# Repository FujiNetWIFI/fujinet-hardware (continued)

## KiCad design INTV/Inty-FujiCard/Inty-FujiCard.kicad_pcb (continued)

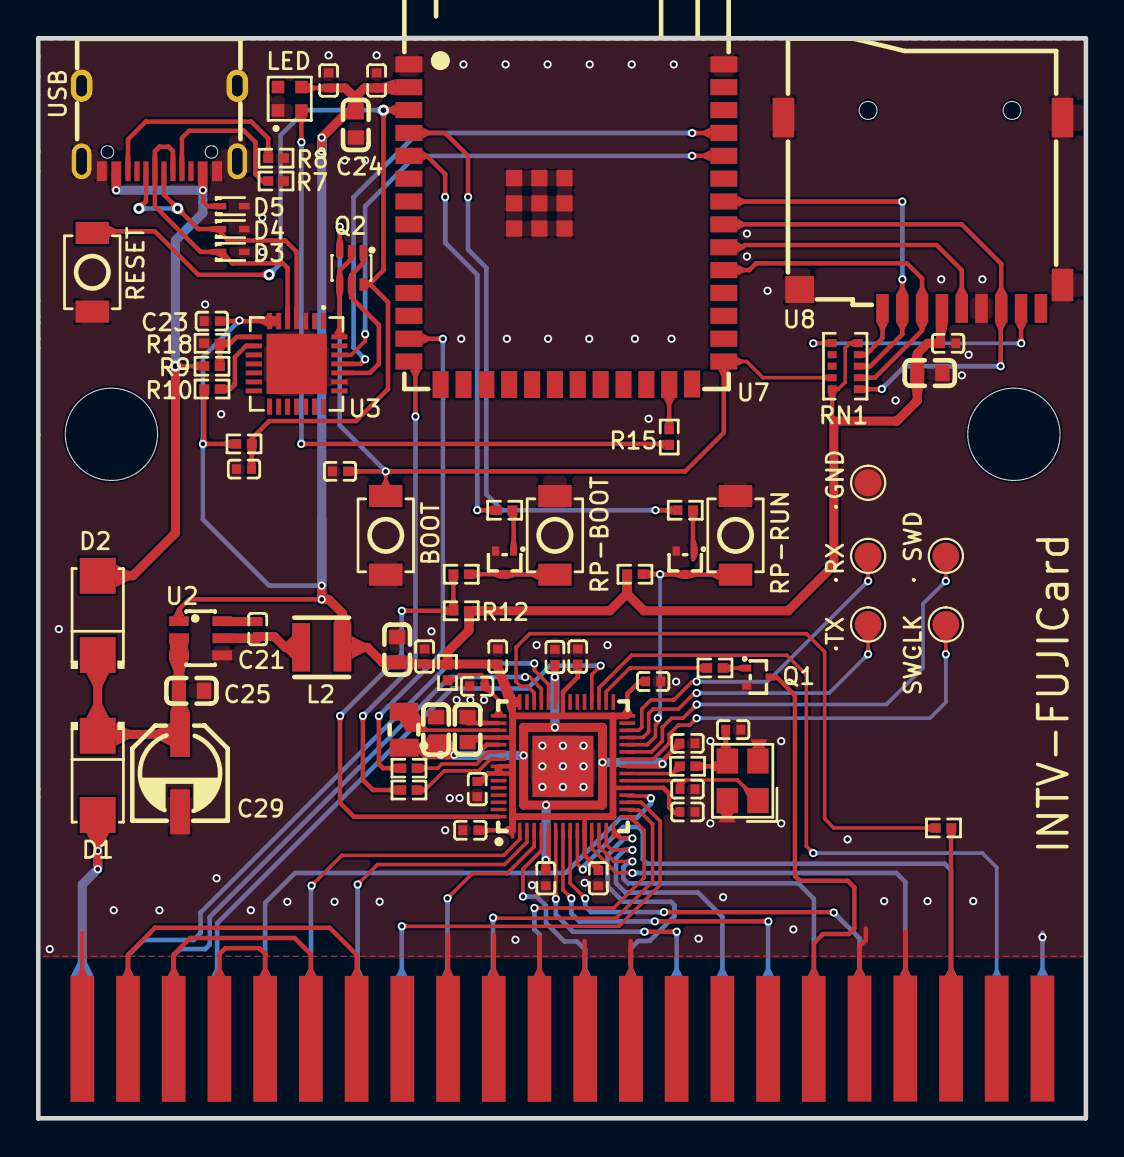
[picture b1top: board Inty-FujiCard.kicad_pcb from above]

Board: 2 copper layers, 58.2 x 60.0 mm, 78 parts (0 on the bottom side), 76 nets.

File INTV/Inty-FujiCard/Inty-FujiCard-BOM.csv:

Qty,References,Value,Footprint,MPN,Manufacturer,LCSC,Description,Notes
17,C1 C3 C7 C8 C9 C10 C11 C12 C13 C14 C15 C16 C21 C22 C23 C26 C27,100nF,C0402,CL05B104KO5NNNC,SAMSUNG,C1525,capacitor (several uses: see schematic),
1,C2,1uF,C0402,CL05A105KA5NQNC,SAMSUNG,C52923,EN power-on delay,
2,C4 C24,22uF,C0603,CL10A226MQ8NRNC,SAMSUNG,C59461,capacitor (several uses: see schematic),
2,C5 C6,15pF,C0402,0402CG150J500NT,FH,C1548,crystal load,
2,C17 C18,4.7uF,C0603,CL10A475KO8NNNC,SAMSUNG,C19666,capacitor (several uses: see schematic),
1,C19,4.7uF,C0402,CL05A475MP5NRNC,SAMSUNG,C23733,VREG_AVDD RC filter (C_FILT),
2,C25 C28,10uF,C0603,CL10A106KP8NNNC,SAMSUNG,C19702,capacitor (several uses: see schematic),
1,C29,100uF,CAP-SMD_BD5.0-L5.3-W5.3-RD,VE-101M1ATR-0505,Lelon,C134722,VIN bulk,
2,D1 D2,SS34,SMA_L4.3-W2.6-LS5.2-RD,SS34,MDD,C8678,diode (several uses: see schematic),
3,D3 D4 D5,ESD5Z5.0T1G,SOD-523_L1.2-W0.8-LS1.6-RD,ESD5Z5.0T1G,BORN,C343989,diode (several uses: see schematic),
1,D6,SK6805-EC20,LED-SMD_4P-L2.0-W2.0-TL_J-ST2020RGB-IC-P4-5-SO1,SK6805-EC20,OPSCO Optoelectronics,C2890036,"status LED (IO48), on 3V3",
2,H1 H2,Hole_D5.127mm,Hole_D5.127mm_NPTH,,,,"shell post hole, 5.127 mm NPTH",not in BOM
1,J1,USB-C,USB-C-SMD_TYPE-C-6PIN-2MD-073,TYPE-C 16PIN 2MD(073),SHOU HAN,C2765186,power + S3 programming / console,
1,K1,INTV_Cart_Edge_44,PCB_EDGE_CONNECTOR_22X2,,,,"Intellivision cartridge edge, 2 x 22 gold fingers, 2.54 mm: A1-A22 component face, B1-B22 back",not in BOM
1,L1,3.3uH,IND-SMD_L2.0-W1.6_AOTA-B201610S3R3-101-T,AOTA-B201610S3R3-101-T,ABRACON,C42411119,RP2350 core SMPS inductor,
1,L2,4.7uH,IND-SMD_L3.0-W3.0-1,YNR3015-4R7M,YJYCOIN,C340361,buck inductor,
3,Q1 Q3 Q4,BC847BT,SOT-523-3_L1.6-W0.8-P1.00-LS1.6-BR,BC847BT,Slkor,C5186022,transistor (several uses: see schematic),
1,Q2,UMH3NTN,SOT-363_L2.0-W1.3-P0.65-LS2.1-TL,UMH3NTN,ROHM,C123008,esptool auto-program (DevKitC-1 style),
7,R1 R2 R5 R10 R11 R13 R16,1k,R0402,0402WGF1001TCE,UNI-ROYAL,C11702,resistor (several uses: see schematic),
3,R3 R4 R6,27R,R0402,0402WGF270JTCE,UNI-ROYAL,C25100,resistor (several uses: see schematic),
2,R7 R8,5.1k,R0402,0402WGF5101TCE,UNI-ROYAL,C25905,resistor (several uses: see schematic),
1,R9,22.1k,R0402,AC0402FR-0722K1L,YAGEO,C226356,VBUS sense divider,
3,R12 R14 R17,10k,R0402,0402WGF1002TCE,UNI-ROYAL,C25744,resistor (several uses: see schematic),
1,R15,330R,R0402,0402WGF3300TCE,UNI-ROYAL,C25104,status LED data series,
1,R18,47.5k,R0402,RC0402FR-0747K5L,YAGEO,C137974,VBUS sense divider,
1,RN1,8x10k,RES-ARRAY-SMD_1206-L3.2-W1.6-P0.64,YC158TJR-0710KL,YAGEO,C309679,"pull-ups: microSD lines, S3 IO0",
4,SW1 SW2 SW3 SW4,TS-1088-AR02016,SW-SMD_L3.9-W3.0-P4.45,TS-1088-AR02016,XUNPU,C720477,push button (several uses: see schematic),
1,TP1,GND,TESTPOINT_PAD_D1.5MM,,,,test pad: GND,not in BOM
1,TP2,TX,TESTPOINT_PAD_D1.5MM,,,,test pad: GP16 (silk TX),not in BOM
1,TP3,RX,TESTPOINT_PAD_D1.5MM,,,,test pad: GP17 (silk RX),not in BOM
1,TP4,SWD,TESTPOINT_PAD_D1.5MM,,,,test pad: SWDIO,not in BOM
1,TP5,SWCLK,TESTPOINT_PAD_D1.5MM,,,,test pad: SWCLK,not in BOM
1,U1,RP2354A,QFN-60_L7.0-W7.0-P0.40-TL-EP3.4,RP2354A,Raspberry Pi,C41378174,RP2354A: serves the Intellivision cartridge bus (fujicard),
1,U2,AP63203WU,TSOT-26_L2.9-W1.6-P0.95-LS2.8-BL,AP63203WU-7,DIODES,C780769,3.3V 2A buck: the whole board,
1,U3,CP2102N-A02-GQFN28,QFN-28_L5.0-W5.0-P0.50-TL-EP3.3,CP2102N-A02-GQFN28R,SKYWORKS/SILICON LABS,C964632,USB-UART for S3 flashing / console (self-powered),
1,U5,12MHz,CRYSTAL-SMD_4P-L3.2-W2.5-BL,ABM8-272-T3,ABRACON,C20625731,RP2354A 12 MHz crystal,
1,U7,ESP32-S3-WROOM-1-N16R8,WIRELM-SMD_ESP32-S3-WROOM-1,ESP32-S3-WROOM-1-N16R8,ESPRESSIF,C2913202,FujiNet core (fujiversal-intv),
1,U8,microSD,SIM-SMD_LX_XDFP-0090-012,TF-CARD-9P,BXCONN,C53144700,"microSD push-push, SPI mode (card detect unused)",

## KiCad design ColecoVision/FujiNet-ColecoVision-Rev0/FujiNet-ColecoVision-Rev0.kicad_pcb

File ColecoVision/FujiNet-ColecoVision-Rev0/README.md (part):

# FujiNet-ColecoVision Rev0

FujiNet for the ColecoVision (and the ADAM's cartridge slot), on one cartridge.
- **RP2350A + W25Q16:** serves the Z80's cartridge bus (`fujinet-firmware/pico/coleco`): A0-A14 straight off the 5 V edge, D0-D7 through a 74LVC245A whose /OE is the AND of the four cart selects.
- **ESP32-S3:** the FujiNet (`fujiversal-coleco`) and the RP's USB host, on the same board.
- **Also on the board:** a microSD, a WS2812 status light, and a USB-C with a CP2102N bridge for flashing and powering it.

**Status (2026-11-05): board routed on 4 layers, JLCPCB and PCBWay packages generated, every gate passing. Nothing has been built yet.**
- **Board:** 4 layers, 40.2 x 82.4 mm, the ColecoVision cart outline (the whole bottom edge carries 2 x 15 gold fingers), four side notches for the shell's ribs. Assembled by JLCPCB or PCBWay, top side only.
- **Firmware:** the schematic implements `pico/coleco/firmware/include/coleco_cart.h` as it stands on fujinet-firmware master. The board file and S3 pin map it still needs are under *Firmware changes this board needs*.
- **Edge:** checked against MAME's slot table and two built, open carts (`tools/audit/edge_orientation.py`); not provisional.
- **Shell:** fits a printed shell (`case/`). An original Coleco shell is unverified: see *Original shell*.

| Check (2026-11-05) | Result |
|---|---|
| Drawing checks (`gen_sch.py`) | every sheet wired; 0 crossings on `cart-bus`, `rp-core`, `fujinet`, `power`; 1 on `usb` (esptool's auto-program pair, as on Studio II and the O2) |
| Netlist parity: kicad-cli netlist vs `design.py`, names included | 112 / 112 nets |
| KiCad ERC, all severities | 0 errors, 0 warnings |
| `tools/check_nets.py`: the netlist vs `coleco_cart.h`, `fujiversal-coleco.h` (fujinet-firmware `origin/master`) | 390 checks, 0 failed; 3 NOTE lines (the firmware changes below) |
| `tools/audit/edge_orientation.py`: footprint and netlist vs MAME's slot table, ThatOldNerd's and Commodore-Bench's boards | all pass (`VERIFIED = True`) |
| `tools/audit/margins.py`: Z80 / LS138 levels against the 330R, the LVC parts and the RP, the select-to-buffer timing, VSENSE, the mux threshold, the cart's draw | 0 negative margins (tightest: +0.11 V, the mux's VBUS threshold under a 4.75 V USB source) |
| Routing | 100 % on 4 layers (see *Layout*); 390 vias, 1136 tracks |
| KiCad DRC + schematic parity on the saved zone fills (kicad-cli, and again through the KiCad MCP) | 0 errors, 0 unconnected, 0 parity issues; 3 silk-over-edge warnings (the S3 module's outline at the flush west edge) |
| `tools/check_vias.py`: no via in a foreign SMD pad | 378 vias, 0 failures |
| `tools/audit/layout_checks.py`: the layout's claims measured on the copper | 56 / 56 (regulator corner, decoupling, USB pairs and skew, crystal, QSPI, exposed pads, every finger to its part in at most 4 vias, the CONS_5V island, the S3 antenna strip, the buck loop) |
| `tools/audit/check_gerbers.py`: the zip itself | 0 failures: outline and notches, both finger rows, masks, inner layers, no plated hole inside an In1 / In2 pour of another net (403 holes) |
| `tools/audit/check_fab.py`: JLC and PCBWay BOM / CPL / centroid / drills / order-number text / gerbers / the edge gate | all pass |
| JLCPCB CPL rotations (`tools/audit/jlc/`), measured against each LCSC part's EasyEDA footprint | 43 (footprint, LCSC) pairs, the RP2350A's QFN-60 high-confidence; 6 medium (the two AND gates, AOTA inductor, TS-1187A, BAT54C, USB-C): check them in JLC's preview |
| kicad-happy 2.2.1 (`tools/audit/run_sch_audit.sh`, `run_pcb_audit.sh`), triaged in `docs/design-review-rev0.md` | SPICE 14 / 14; 8 high-rule groups: 3 false positives or by design (keep-out boxes, the fiducial and connectors at the edge, UMH3N decoupling), 1 not a split (+3V3_RP fills as one piece), 3 accepted or minor (bus over In2 island edges, USB layer changes, the USB pair across islands), 1 minor (the USBLC6's VBUS cap 9 mm away) |
| Printed shell (`case/`, OpenSCAD) | `check` and `parts_check` empty, `parts_control` 86 volumes |

## Sheets

Drawn with the FujiNet-StudioII / Arcadia / O2 toolkit:
- **Wires only:** every connection on a sheet is a wire.
- **Rails:** rails are power symbols (`GND`, `CONS_5V`, `VBUS`, `+5V`, `+3V3`, `+3V3_RP`, `DVDD`).
- **Between sheets:** the sheets join only through hierarchical labels, wired on the root's block diagram.

| Page | Sheet | Contents |
|---|---|---|
| 1 | root | the block diagram: rp-core <-> fujinet (USB_DP / USB_DM, RUN_CTL, BOOTSEL_CTL, S3_EN), fujinet <-> usb (S3_TXD / S3_RXD, S3_EN, S3_IO0); notes |
| 2 | `cart-bus` | the 30-finger edge and the RP2350A's GPIO unit row for row: A0-A14 straight through the four 330R arrays; D0-D7 straight through the 74LVC245A; DIR (GP27) from the buffer's foot with its pull-up; the four selects, pulled up, into the 74LVC1G11 + 74LVC1G08, whose /CE rises into the buffer's /OE and runs on to GP26; the console-5V sense (GP28), the activity LED (GP25), the bring-up pads (GP23, GP24, GP29) |
| 3 | `rp-core` | the RP2350A's core unit: a capacitor at every supply pin, Raspberry Pi's regulator corner, the W25Q16 standing over the QSPI pins, crystal, SWD, RUN / BOOTSEL / RESET (the BAT54C to S3 EN), the USB 27R pair out to the S3 |
| 4 | `fujinet` | ESP32-S3-WROOM-1-N16R8, its EN RC and BOOT button, microSD, WS2812 |
| 5 | `usb` | USB-C, USBLC6-2SC6, CP2102N, esptool's auto-program pair |
| 6 | `power` | TPS2116 power mux (USB first, console 5 V second), the S3's AP63203 buck, the RP's AP2112K LDO, rail test pads |

## Edge connector

30 contacts in two rows of 15 at 2.54 mm. The **even pins** are on the component face, the **odd pins** behind them (pin 1 behind pin 2). Seen from the component face with the contacts down, pins 1 / 2 are at the left.

| Pin | Signal | Board net | Pin | Signal | Board net |
|---|---|---|---|---|---|
| 1, 3, 5 | D2, D1, D0 | '245 A2, A1, A0 | 2 | /C000 | 10k up; 74LVC1G11 |
| 7, 9, 11 | A0, A1, A2 | 330R -> GP0-2 | 4-12 | D3-D7 | '245 A3-A7 |
| 13 | SHLD (ADAM: RF ground) | GND | 14, 16 | A11, A10 | 330R -> GP11, GP10 |
| 15, 17 | A3, A4 | 330R -> GP3, GP4 | 18 | /8000 | 10k up; 74LVC1G11 |
| 19 | A13 | 330R -> GP13 | 20 | A14 | 330R -> GP14 |
| 21-25 | A5, A6, A7 | 330R -> GP5-7 | 22 | /A000 | 10k up; 74LVC1G11 |
| 27 | /E000 | 10k up; 74LVC1G08 | 24, 26, 28 | A12, A9, A8 | 330R -> GP12, GP9, GP8 |
| 29 | GND | GND | 30 | +5V | CONS_5V -> TPS2116 VIN2 (this finger starts 1.5 mm in: it mates last) |

No /RD, /WR, A15, clock or reset reach the cart. The selects come from the console's '138, enabled by /MREQ and RFSH: a write selects as a read does, refresh never.

**Sources:**
- **Pinout:** MAME `src/devices/bus/coleco/cartridge/exp.h`, the same as the Coleco ADAM Technical Reference Manual's J1 (CS1*-CS4* = /8000 /A000 /C000 /E000).
- **Two built, open carts**, read from their design files (numbers and names only, no file copied): ThatOldNerd's Coleco-Game-Cart V4 (GPL-3.0, Eagle) and Commodore-Bench's ColecoVision Reprogrammable Flash Card (MIT, KiCad; aotta's PiCOLECO uses the same footprint). Joe Grand's "Pixels Past" cart ("fits standard housing") for the width and the notches.
- `tools/audit/edge_orientation.py` checks the footprint and the netlist against all of them (and a local MAME tree when there is one). It passes, so `tools/edge_geom.VERIFIED` is True.

**Geometry (`tools/edge_geom.py`):**
- 15 fingers per face at 2.54 mm, 1.6 mm wide, from 0.5 mm in (the bevel) to 8.5 mm; the +5V finger from 1.5 mm (Commodore-Bench's practice: GND mates first); 1.6 mm board (the slot takes 1.57 +- 0.2 mm);
- the 40.2 x 82.4 mm outline: built carts are 40.0-40.64 wide; Commodore-Bench's / PiCOLECO's length, so the USB-C and the microSD reach the shell's top wall;
- four 2.0 mm side notches at the widest published spans (ThatOldNerd's): 19.6-26.0 mm up on both sides, 34.0-40.5 (pin-1 side) and 36.5-43.0 (pin-30 side);
- no part closer than 15 mm to the edge (ThatOldNerd's lowest pads sit at 15, Commodore-Bench's lowest parts at 17).

## RP2350A pin map

Exactly `coleco_cart.h`. `tools/check_nets.py` reads it from fujinet-firmware `origin/master` and checks every pin.

| GPIO | Net | Goes to |
|---|---|---|
| 0-14 | RP_A0-14 | 330R -> A0-A14 (`ADDR_MASK` 0x7FFF; 5 V-tolerant pads) |
| 15-22 | RP_D0-7 | the 74LVC245A's B port (`D0_PIN` 15) |
| 23 | GP23 | test pad (spare) |
| 24 | DBG_TX | test pad, UART1 TX, 3.3 V |
| 25 | RP_LED | 680R, red LED (`PICO_DEFAULT_LED_PIN`) |
| 26 | CART_CE_N | the AND of /8000 /A000 /C000 /E000 (`CE_PIN`), also the '245's /OE |
| 27 | BUF_DIR | the '245's DIR, 1 = console -> cart (`DIR_PIN`), 10k pull-up |
| 28 | VSENSE | console 5 V through 10k / 15k (3.0 V at 5 V), 100 nF (`PWR_PIN`, read as a digital input) |
| 29 | SELFTEST | test pad |
| QSPI | QSPI_SS / SCLK / SD0-3 | W25Q16JV (2 MB), its /CS the BOOTSEL strap |
| USB | RP_USB_DP / DM | 27R -> the ESP32-S3's USB host (IO20 / IO19), on the board |
| RUN, QSPI_SS | | 10k pull-ups; RESET / BOOTSEL buttons; 1k from S3 IO4 / IO5 |

**The bus side.** core1 drives GP15-22 off the bare address on every cycle, RAM and BIOS cycles included (`coleco_cart.c`), so the data buffer's /OE must be the hardware select: the 74LVC1G11 + 74LVC1G08 AND the four selects (no 74LVC21 is stocked at JLCPCB). The '245 and the gates run at 3.3 V with 5 V-tolerant inputs (`coleco_cart.h` asks for an LVC part, not HCT). DIR's pull-up keeps the buffer facing the RP while the RP is in reset, and the firmware holds it there while the console is off (its unpowered '138 reads as every select low). `tools/audit/margins.py` has the levels and the timing (the gates and the buffer's enable add under 30 ns against the ~285 ns the firmware has after /CE falls).

**Why the RP2350A + W25Q16:** on 2026-11-04 the RP2354A (C41378174) and RP2354B (C39843328), the stacked-flash parts the sister carts use, were out of stock at JLCPCB and LCSC; the RP2350A (C42411118) and the W25Q16JVUXIQ (C2843335) were in stock. The QFN-60's GPIO0-25 are 5 V tolerant; GP26-28 (/CE, DIR, PWR) only ever see 3.3 V. The RP2350's 520 KB SRAM lifts the firmware's 128K image cap (an RP2040 limit).

## ESP32-S3 pin map

`include/pinmap/fujiversal-coleco.h` (SD 38-41, UART0 43/44, LED strip 48), plus what every on-cart S3 board adds:

| S3 pin | Net | Goes to |
|---|---|---|
| IO19 / IO20 | USB_DM / USB_DP | the RP2350A's USB through its 27R (the S3 is the host) |
| IO38 / 39 / 40 / 41 | SD_MOSI / SCK / MISO / CS | microSD (SPI), 10k pull-ups on CS, DO, DAT1, DAT2 |
| IO42 | SD_CD | card detect, 10k pull-up (low = card in) |
| IO48 | LED_STRIP | 330R -> WS2812B-2020 (on +5V; VIH 2.7 V takes 3.3 V data) |
| TXD0 / RXD0 | S3_TXD / S3_RXD | CP2102N |
| IO4 / IO5 | RUN_CTL / BOOTSEL_CTL | 1k -> RP RUN / QSPI_SS: the S3 can reset the RP into its USB boot ROM |
| EN / IO0 | S3_EN / S3_IO0 | EN RC (10k / 1 uF), RESET (through the BAT54C), the BOOT button, the auto-program pair |

There is no separate S3 EN button (the sister carts have one): RESET pulls EN low through the BAT54C, and the 40 mm board has no room for a fourth switch.

## Power

| Rail | Source | Feeds |
|---|---|---|
| `CONS_5V` | edge pin 30 (the console's 5 V) | TPS2116 VIN2, the VSENSE divider |
| `VBUS` | USB-C (USBLC6, 1 uF + 100 nF) | TPS2116 VIN1 (priority), CP2102N VBUS sense |
| `+5V` | **TPS2116 mux**: VBUS above 3.96-4.64 V first (MODE on VIN1, PR1 33k / 10k), else the console | the buck, the RP LDO, the WS2812 |
| `+3V3` | AP63203 3.3 V / 2 A buck | ESP32-S3, CP2102N, microSD |
| `+3V3_RP` | AP2112K-3.3 LDO | every RP2350A supply pin, the W25Q16, the 74LVC245A and the AND gates |
| `DVDD` | RP2350 core SMPS (3.3 uH) | RP core, 1.1 V |

**Load:** without USB, ~145 mA average and ~370 mA in WiFi bursts at 5 V (`margins.py`). The ADAM's Technical Reference Manual rates its cart slot at "typical available current 0.2A"; the ColecoVision's figure is not published. **Prefer USB-C power during play.** The mux blocks reverse current both ways: a cart on USB never powers a console that is off.

## Layout

- **Stack (4 layers, JLC04161H-7628):** F.Cu signals + GND pour (even fingers); In1 GND; In2 +5V with a +3V3 island (the upper half: module, CP2102N, microSD, buck output, and a tongue under the module's foot for its decoupling), a +3V3_RP island (the lower half: RP, flash, bus logic, LDO output), a DVDD island under the RP's core, and a CONS_5V strip from the +5V finger up the east edge to the mux; B.Cu signals + GND pour (odd fingers). Inner planes stop above the finger field; the finger field is a rule area on both faces.
- **Placement (`tools/placement.py`):**
  - **Top edge:** the USB-C (west of centre) and the microSD (east), both reaching the shell's top wall; the CP2102N block between the USB-C and the module.
  - **Upper body:** the ESP32-S3 turned 90 degrees, its antenna flush with the west edge over a strip that is copper-free on every layer, 15 mm either side of the module's centre line (the footprint's own keep-out is 24 mm: narrowed here, the board is 40 mm wide); east of it the buck, RESET and S3 BOOT, the WS2812.
  - **Lower body:** the RP2350A at 90 degrees in FujiNet-Arcadia Rev0's neighbourhood (decoupling north, crystal east, Raspberry Pi's regulator corner west, turned with it), the W25Q16 west of it where Raspberry Pi's minimal design has its flash; the four address arrays under it in GPIO order, inputs toward the fingers; the 74LVC245A in the south-west corner, straight over the data fingers (the edge's D0-D7 are its west end; GP15-22's lines cross under the address lines); the select pull-ups and the AND pair east of the arrays, with the bring-up pads; the mux by the +5V finger's column; BOOTSEL on the west edge.
  - **Band above the fingers (y 115-120.5):** parts-free (the shell's bottom). It carries the buses.
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
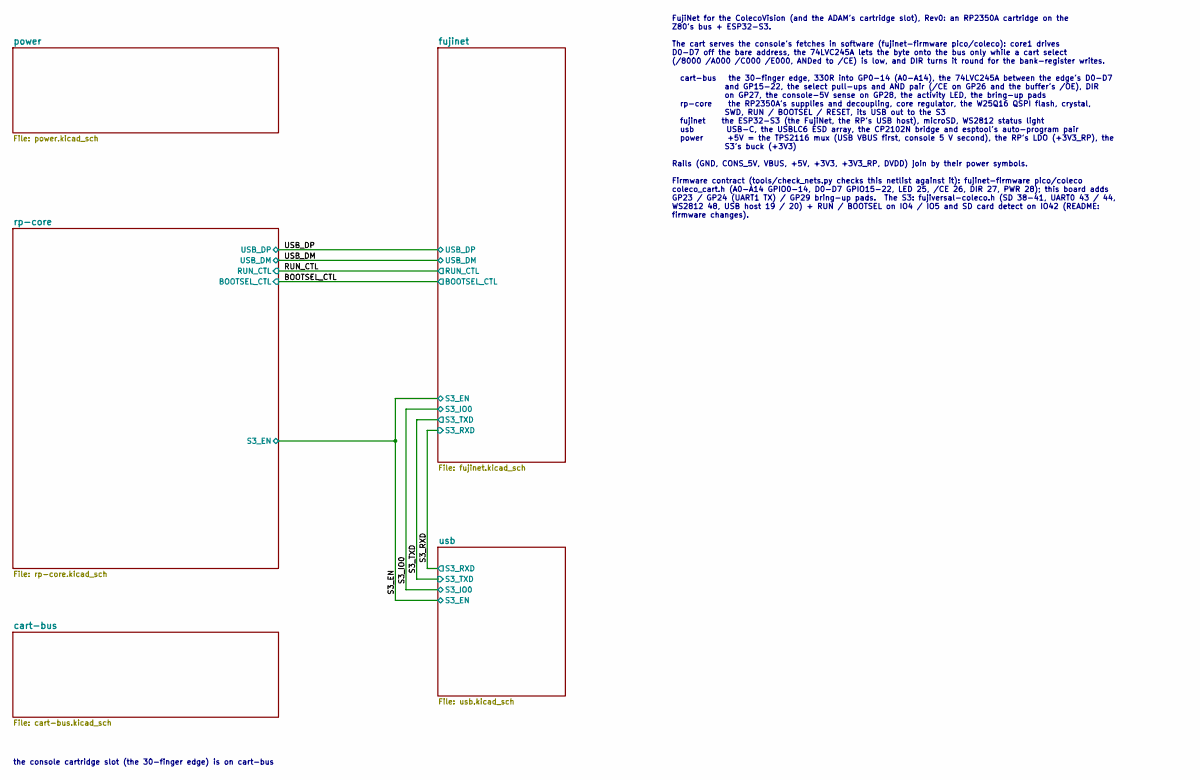
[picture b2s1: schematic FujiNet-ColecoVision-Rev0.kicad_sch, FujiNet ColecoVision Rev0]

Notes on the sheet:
the console cartridge slot (the 30-finger edge) is on cart-bus
FujiNet for the ColecoVision (and the ADAM's cartridge slot), Rev0: an RP2350A cartridge on the Z80's bus + ESP32-S3. The cart serves the console's fetches in software (fujinet-firmware pico/coleco): core1 drives D0-D7 off the bare address, the 74LVC245A lets the byte onto the bus only while a cart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

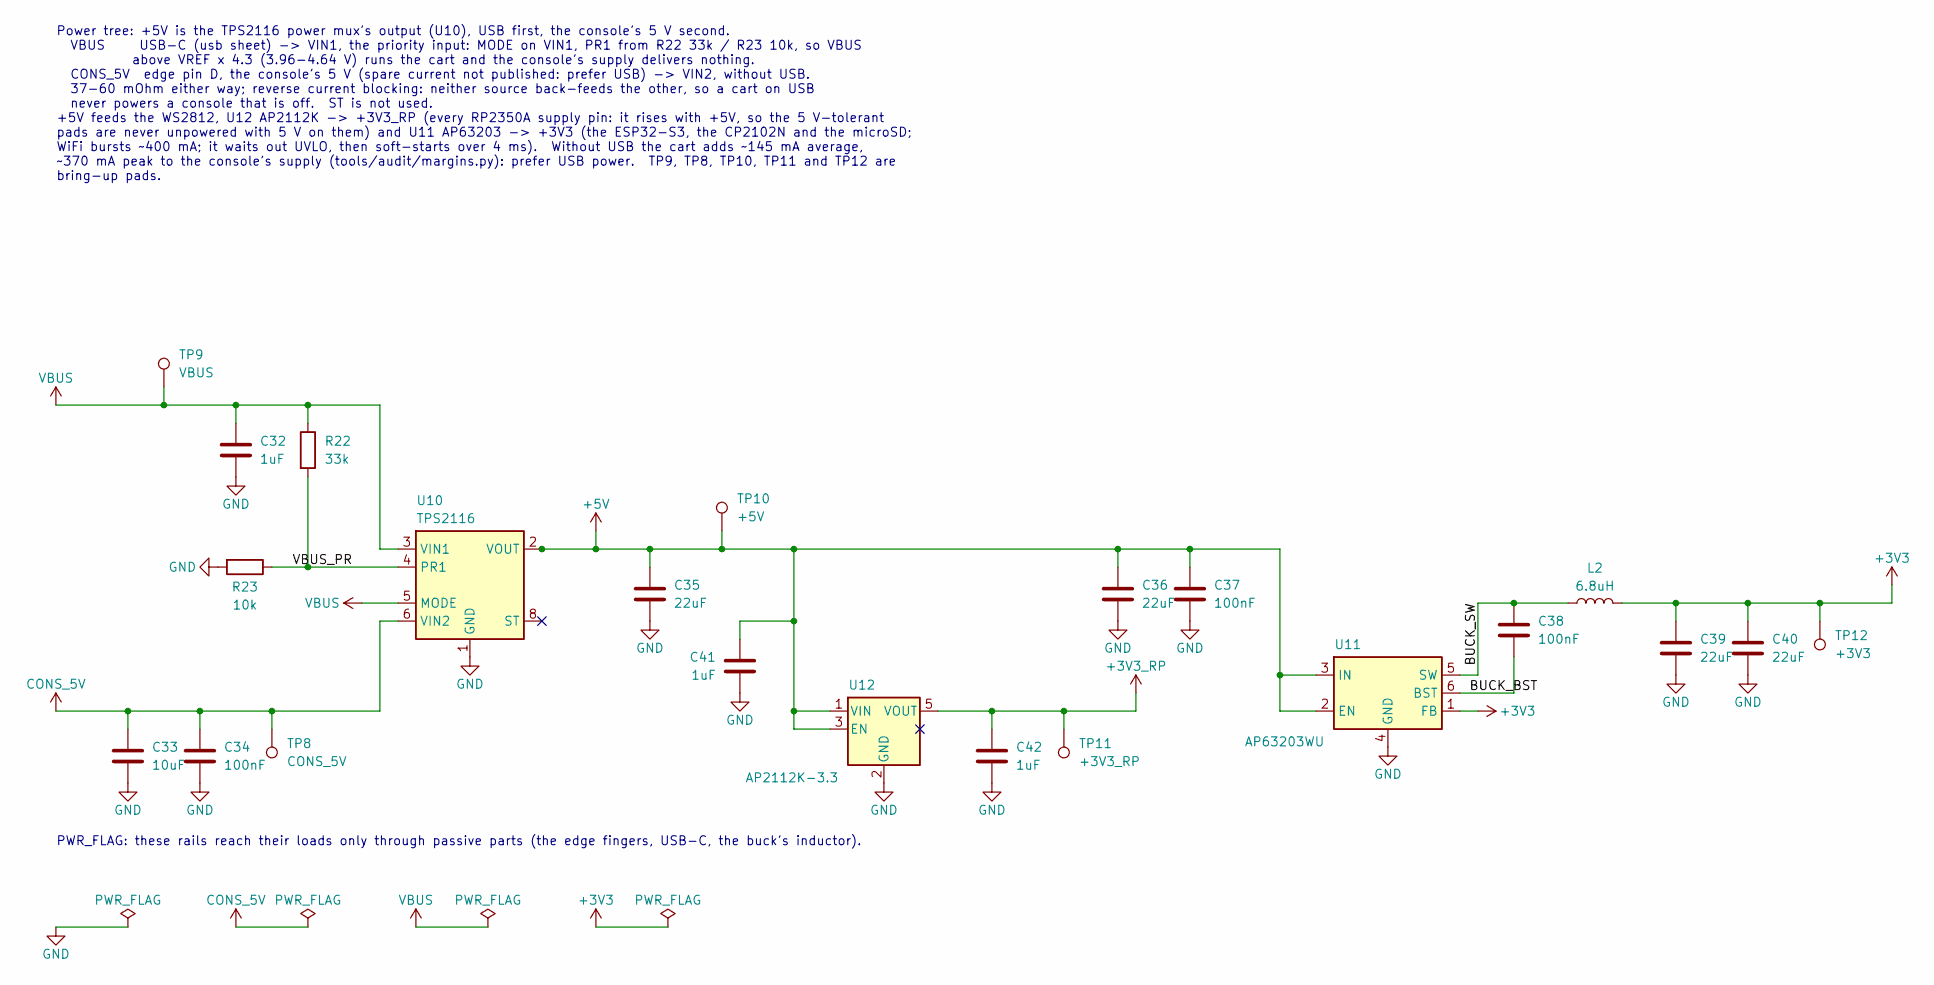
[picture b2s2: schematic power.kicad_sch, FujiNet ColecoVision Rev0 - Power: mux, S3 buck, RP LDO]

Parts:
C32, C41, C42: 1uF; C_0603_1608Metric; MPN CL10A105KB8NNNC; LCSC C15849
C33: 10uF; C_0603_1608Metric; MPN CL10A106KP8NNNC; LCSC C19702
C34, C37, C38: 100nF; C_0603_1608Metric; MPN CC0603KRX7R9BB104; LCSC C14663
C35, C36, C39, C40: 22uF; C_0805_2012Metric; MPN CL21A226MAQNNNE; LCSC C45783
L2: 6.8uH; L_Sunlord_SWPA4030S; MPN SWPA4030S6R8MT; LCSC C62684
R22: 33k; R_0603_1608Metric; MPN 0603WAF3302T5E; LCSC C4216
R23: 10k; R_0603_1608Metric; MPN 0603WAF1002T5E; LCSC C25804
TP8: CONS_5V; TestPoint_Pad_D1.5mm
TP9: VBUS; TestPoint_Pad_D1.5mm
TP10: +5V; TestPoint_Pad_D1.5mm
TP11: +3V3_RP; TestPoint_Pad_D1.5mm
TP12: +3V3; TestPoint_Pad_D1.5mm
U10: TPS2116; SOT-583-8; MPN TPS2116DRLR; LCSC C3235557
U11: AP63203WU; TSOT-23-6; MPN AP63203WU-7; LCSC C780769
U12: AP2112K-3.3; SOT-23-5; MPN AP2112K-3.3TRG1; LCSC C51118

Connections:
+3V3: C39.1, C40.1, L2.2, TP12.1, U11.1 (FB); also elsewhere on the board
+3V3_RP: C42.1, TP11.1, U12.5 (VOUT); also elsewhere on the board
+5V: C35.1, C36.1, C37.1, C41.1, TP10.1, U10.2 (VOUT), U10.7 (VOUT), U11.2 (EN), U11.3 (IN), U12.1 (VIN), U12.3 (EN); also elsewhere on the board
/power/BUCK_BST: C38.2, U11.6 (BST)
/power/BUCK_SW: C38.1, L2.1, U11.5 (SW)
/power/VBUS_PR: R22.2, R23.1, U10.4 (PR1)
CONS_5V: C33.1, C34.1, TP8.1, U10.6 (VIN2); also elsewhere on the board
GND: C32.2, C33.2, C34.2, C35.2, C36.2, C37.2, C39.2, C40.2, C41.2, C42.2, R23.2, U10.1 (GND), U11.4 (GND), U12.2 (GND); also elsewhere on the board
VBUS: C32.1, R22.1, TP9.1, U10.3 (VIN1), U10.5 (MODE); also elsewhere on the board

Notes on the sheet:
PWR_FLAG: these rails reach their loads only through passive parts (the edge fingers, USB-C, the buck's inductor).
Power tree: +5V is the TPS2116 power mux's output (U10), USB first, the console's 5 V second. VBUS USB-C (usb sheet) -> VIN1, the priority input: MODE on VIN1, PR1 from R22 33k / R23 10k, so VBUS above VREF x 4.3 (3.96-4.64 V) runs the cart and the console's supply delivers nothing. CONS_5V edge pi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

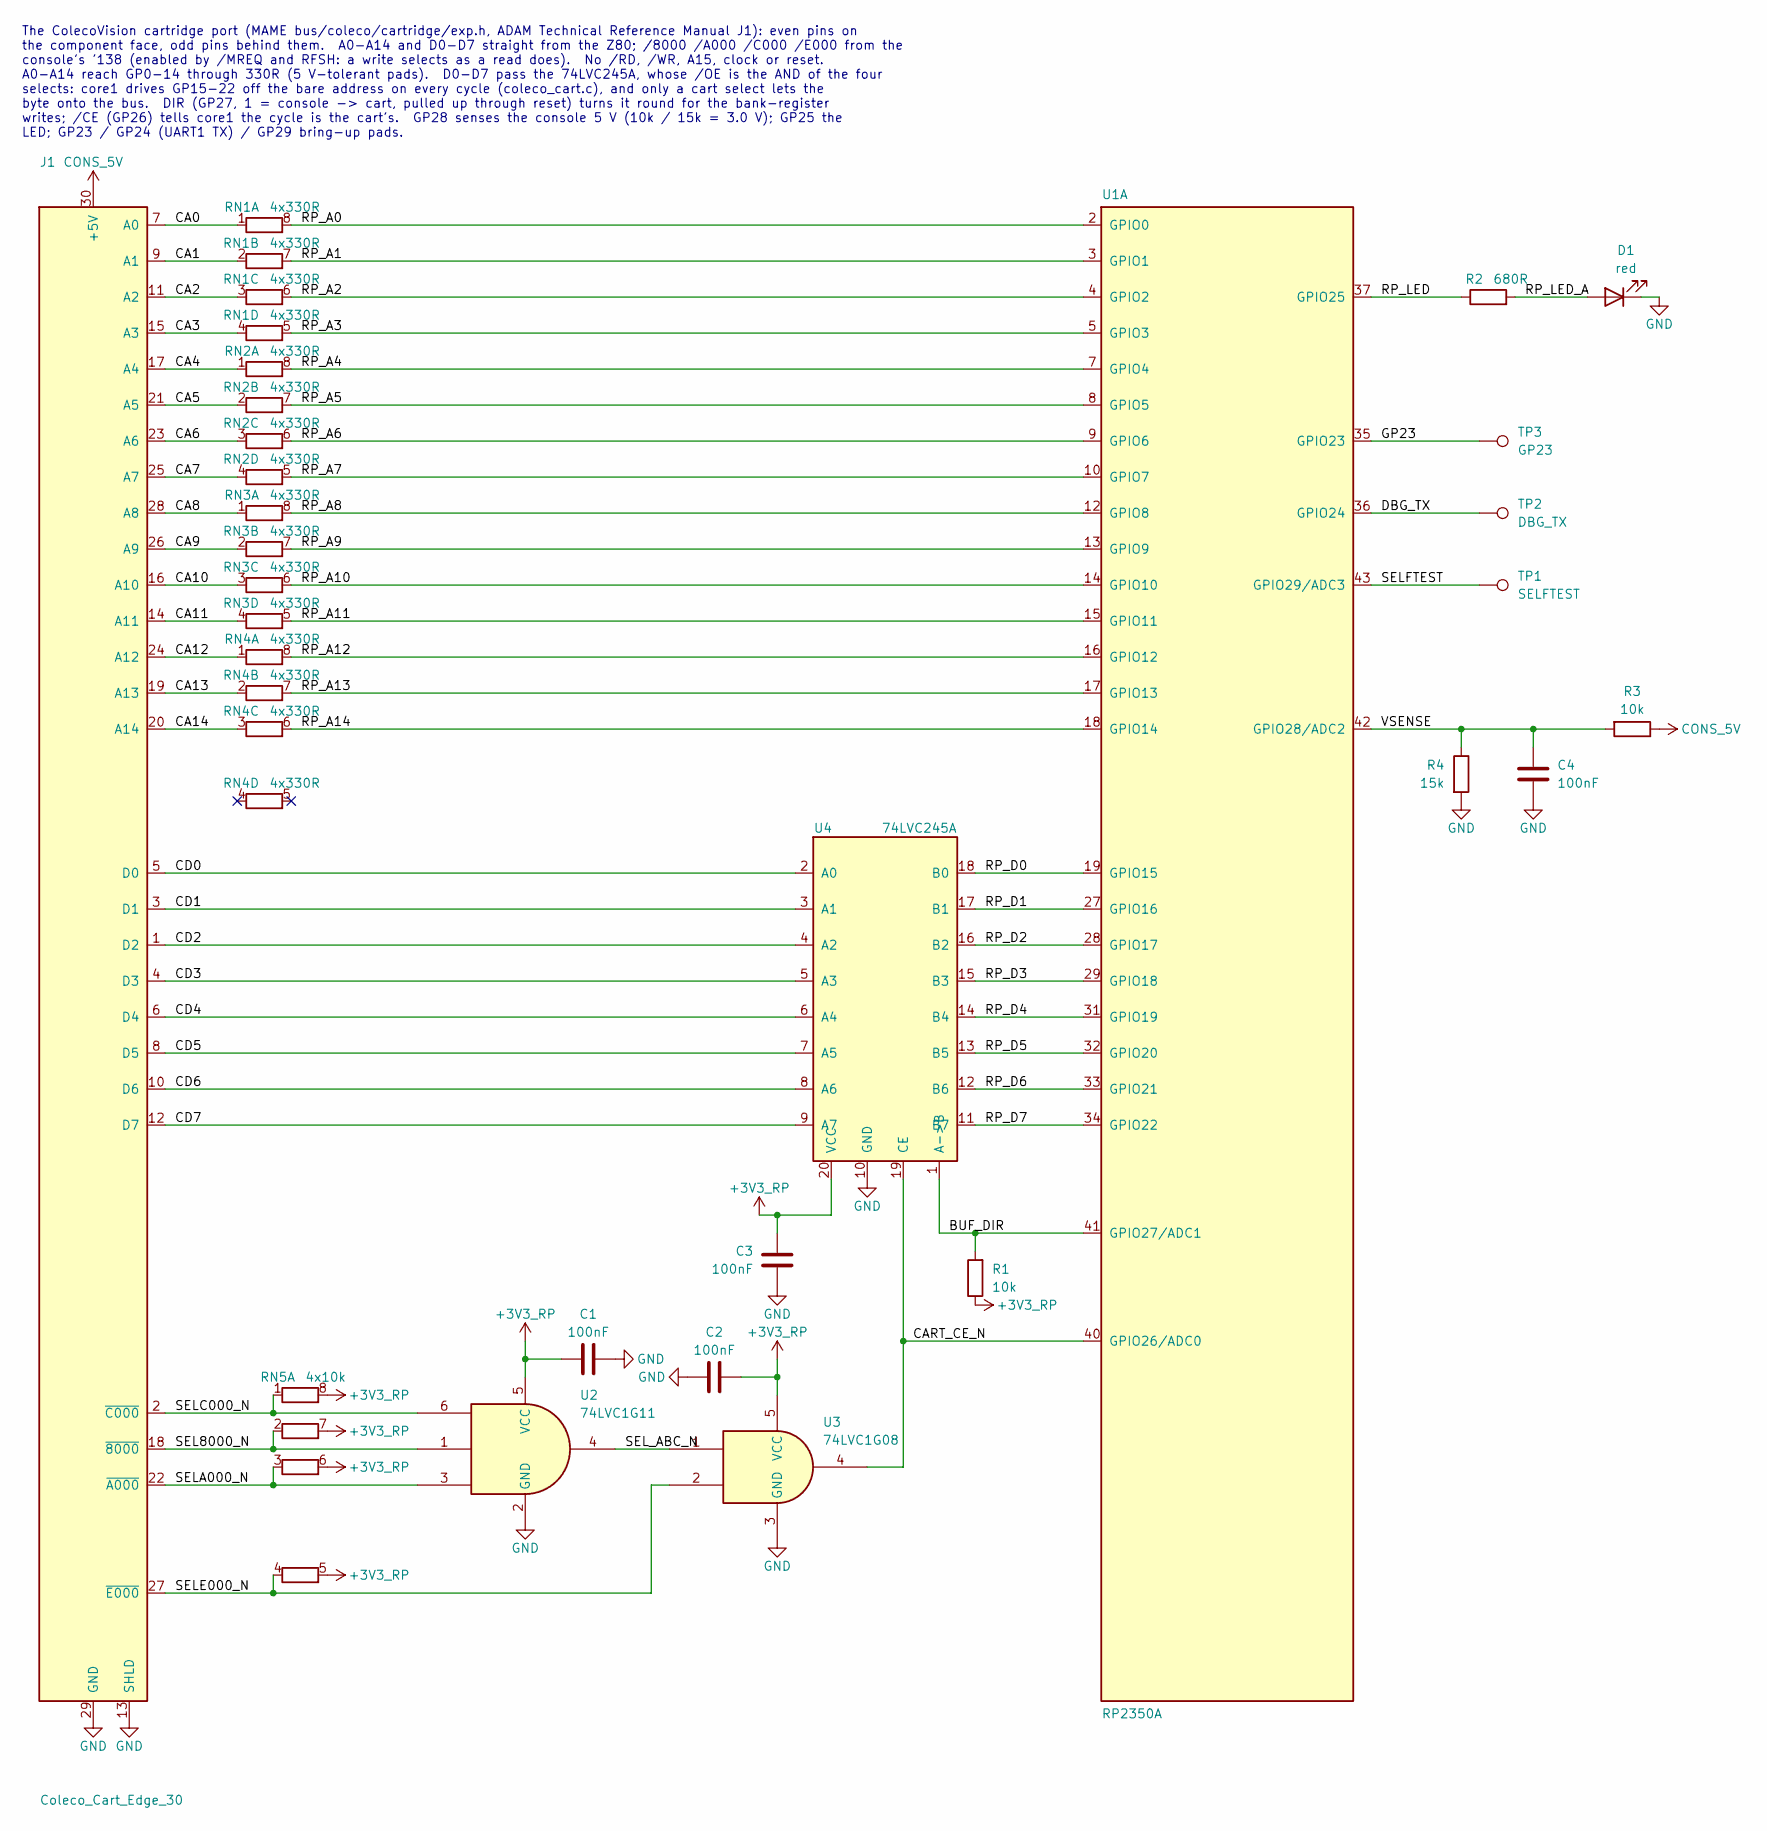
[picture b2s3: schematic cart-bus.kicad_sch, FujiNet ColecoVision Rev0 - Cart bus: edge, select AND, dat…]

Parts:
C1, C2, C3, C4: 100nF; C_0603_1608Metric; MPN CC0603KRX7R9BB104; LCSC C14663
D1: red; LED_0603_1608Metric; MPN KT-0603R; LCSC C2286
J1: Coleco_Cart_Edge_30
R1, R3: 10k; R_0603_1608Metric; MPN 0603WAF1002T5E; LCSC C25804
R2: 680R; R_0603_1608Metric; MPN 0603WAF6800T5E; LCSC C23228
R4: 15k; R_0603_1608Metric; MPN 0603WAF1502T5E; LCSC C22809
RN1, RN2, RN3, RN4: 4x330R; R_Array_Convex_4x0603; MPN 4D03WGJ0331T5E; LCSC C12018
RN5: 4x10k; R_Array_Convex_4x0603; MPN 4D03WGJ0103T5E; LCSC C29718
TP1: SELFTEST; TestPoint_Pad_D1.5mm
TP2: DBG_TX; TestPoint_Pad_D1.5mm
TP3: GP23; TestPoint_Pad_D1.5mm
U1: RP2350A; RPI_RP2350A_QFN60; MPN RP2350A; LCSC C42411118
U2: 74LVC1G11; SOT-23-6; MPN SN74LVC1G11DBVR; LCSC C22046
U3: 74LVC1G08; SOT-23-5; MPN SN74LVC1G08DBVR; LCSC C7666
U4: 74LVC245A; TSSOP-20_4.4x6.5mm_P0.65mm; MPN SN74LVC245APWR; LCSC C7848

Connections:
+3V3_RP: C1.1, C2.1, C3.1, R1.1, RN5.5 (R4.2), RN5.6 (R3.2), RN5.7 (R2.2), RN5.8 (R1.2), U2.5 (VCC), U3.5 (VCC), U4.20 (VCC); also elsewhere on the board
/cart-bus/BUF_DIR: R1.2, U1.41 (GPIO27/ADC1), U4.1 (A->B)
/cart-bus/CA0: J1.7 (A0), RN1.1 (R1.1)
/cart-bus/CA1: J1.9 (A1), RN1.2 (R2.1)
/cart-bus/CA2: J1.11 (A2), RN1.3 (R3.1)
/cart-bus/CA3: J1.15 (A3), RN1.4 (R4.1)
/cart-bus/CA4: J1.17 (A4), RN2.1 (R1.1)
/cart-bus/CA5: J1.21 (A5), RN2.2 (R2.1)
/cart-bus/CA6: J1.23 (A6), RN2.3 (R3.1)
/cart-bus/CA7: J1.25 (A7), RN2.4 (R4.1)
/cart-bus/CA8: J1.28 (A8), RN3.1 (R1.1)
/cart-bus/CA9: J1.26 (A9), RN3.2 (R2.1)
/cart-bus/CA10: J1.16 (A10), RN3.3 (R3.1)
/cart-bus/CA11: J1.14 (A11), RN3.4 (R4.1)
/cart-bus/CA12: J1.24 (A12), RN4.1 (R1.1)
/cart-bus/CA13: J1.19 (A13), RN4.2 (R2.1)
/cart-bus/CA14: J1.20 (A14), RN4.3 (R3.1)
/cart-bus/CART_CE_N: U1.40 (GPIO26/ADC0), U3.4, U4.19 (CE)
/cart-bus/CD0: J1.5 (D0), U4.2 (A0)
/cart-bus/CD1: J1.3 (D1), U4.3 (A1)
/cart-bus/CD2: J1.1 (D2), U4.4 (A2)
/cart-bus/CD3: J1.4 (D3), U4.5 (A3)
/cart-bus/CD4: J1.6 (D4), U4.6 (A4)
/cart-bus/CD5: J1.8 (D5), U4.7 (A5)
/cart-bus/CD6: J1.10 (D6), U4.8 (A6)
/cart-bus/CD7: J1.12 (D7), U4.9 (A7)
/cart-bus/DBG_TX: TP2.1, U1.36 (GPIO24)
/cart-bus/GP23: TP3.1, U1.35 (GPIO23)
/cart-bus/RP_A0: RN1.8 (R1.2), U1.2 (GPIO0)
/cart-bus/RP_A1: RN1.7 (R2.2), U1.3 (GPIO1)
/cart-bus/RP_A2: RN1.6 (R3.2), U1.4 (GPIO2)
/cart-bus/RP_A3: RN1.5 (R4.2), U1.5 (GPIO3)
/cart-bus/RP_A4: RN2.8 (R1.2), U1.7 (GPIO4)
/cart-bus/RP_A5: RN2.7 (R2.2), U1.8 (GPIO5)
/cart-bus/RP_A6: RN2.6 (R3.2), U1.9 (GPIO6)
/cart-bus/RP_A7: RN2.5 (R4.2), U1.10 (GPIO7)
/cart-bus/RP_A8: RN3.8 (R1.2), U1.12 (GPIO8)
/cart-bus/RP_A9: RN3.7 (R2.2), U1.13 (GPIO9)
/cart-bus/RP_A10: RN3.6 (R3.2), U1.14 (GPIO10)
/cart-bus/RP_A11: RN3.5 (R4.2), U1.15 (GPIO11)
/cart-bus/RP_A12: RN4.8 (R1.2), U1.16 (GPIO12)
/cart-bus/RP_A13: RN4.7 (R2.2), U1.17 (GPIO13)
/cart-bus/RP_A14: RN4.6 (R3.2), U1.18 (GPIO14)
/cart-bus/RP_D0: U1.19 (GPIO15), U4.18 (B0)
/cart-bus/RP_D1: U1.27 (GPIO16), U4.17 (B1)
/cart-bus/RP_D2: U1.28 (GPIO17), U4.16 (B2)
/cart-bus/RP_D3: U1.29 (GPIO18), U4.15 (B3)
/cart-bus/RP_D4: U1.31 (GPIO19), U4.14 (B4)
/cart-bus/RP_D5: U1.32 (GPIO20), U4.13 (B5)
/cart-bus/RP_D6: U1.33 (GPIO21), U4.12 (B6)
/cart-bus/RP_D7: U1.34 (GPIO22), U4.11 (B7)
/cart-bus/RP_LED: R2.1, U1.37 (GPIO25)
/cart-bus/RP_LED_A: D1.2 (A), R2.2
/cart-bus/SEL8000_N: J1.18 (~8000), RN5.2 (R2.1), U2.1
/cart-bus/SELA000_N: J1.22 (~A000), RN5.3 (R3.1), U2.3
/cart-bus/SELC000_N: J1.2 (~C000), RN5.1 (R1.1), U2.6
/cart-bus/SELE000_N: J1.27 (~E000), RN5.4 (R4.1), U3.2
/cart-bus/SELFTEST: TP1.1, U1.43 (GPIO29/ADC3)
/cart-bus/SEL_ABC_N: U2.4, U3.1
/cart-bus/VSENSE: C4.1, R3.2, R4.1, U1.42 (GPIO28/ADC2)
CONS_5V: J1.30 (+5V), R3.1; also elsewhere on the board
GND: C1.2, C2.2, C3.2, C4.2, D1.1 (K), J1.13 (SHLD), J1.29 (GND), R4.2, U2.2 (GND), U3.3 (GND), U4.10 (GND); also elsewhere on the board

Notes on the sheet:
The ColecoVision cartridge port (MAME bus/coleco/cartridge/exp.h, ADAM Technical Reference Manual J1): even pins on the component face, odd pins behind them. A0-A14 and D0-D7 straight from the Z80; /8000 /A000 /C000 /E000 from the console's '138 (enabled by /MREQ and RFSH: a write selects as a read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

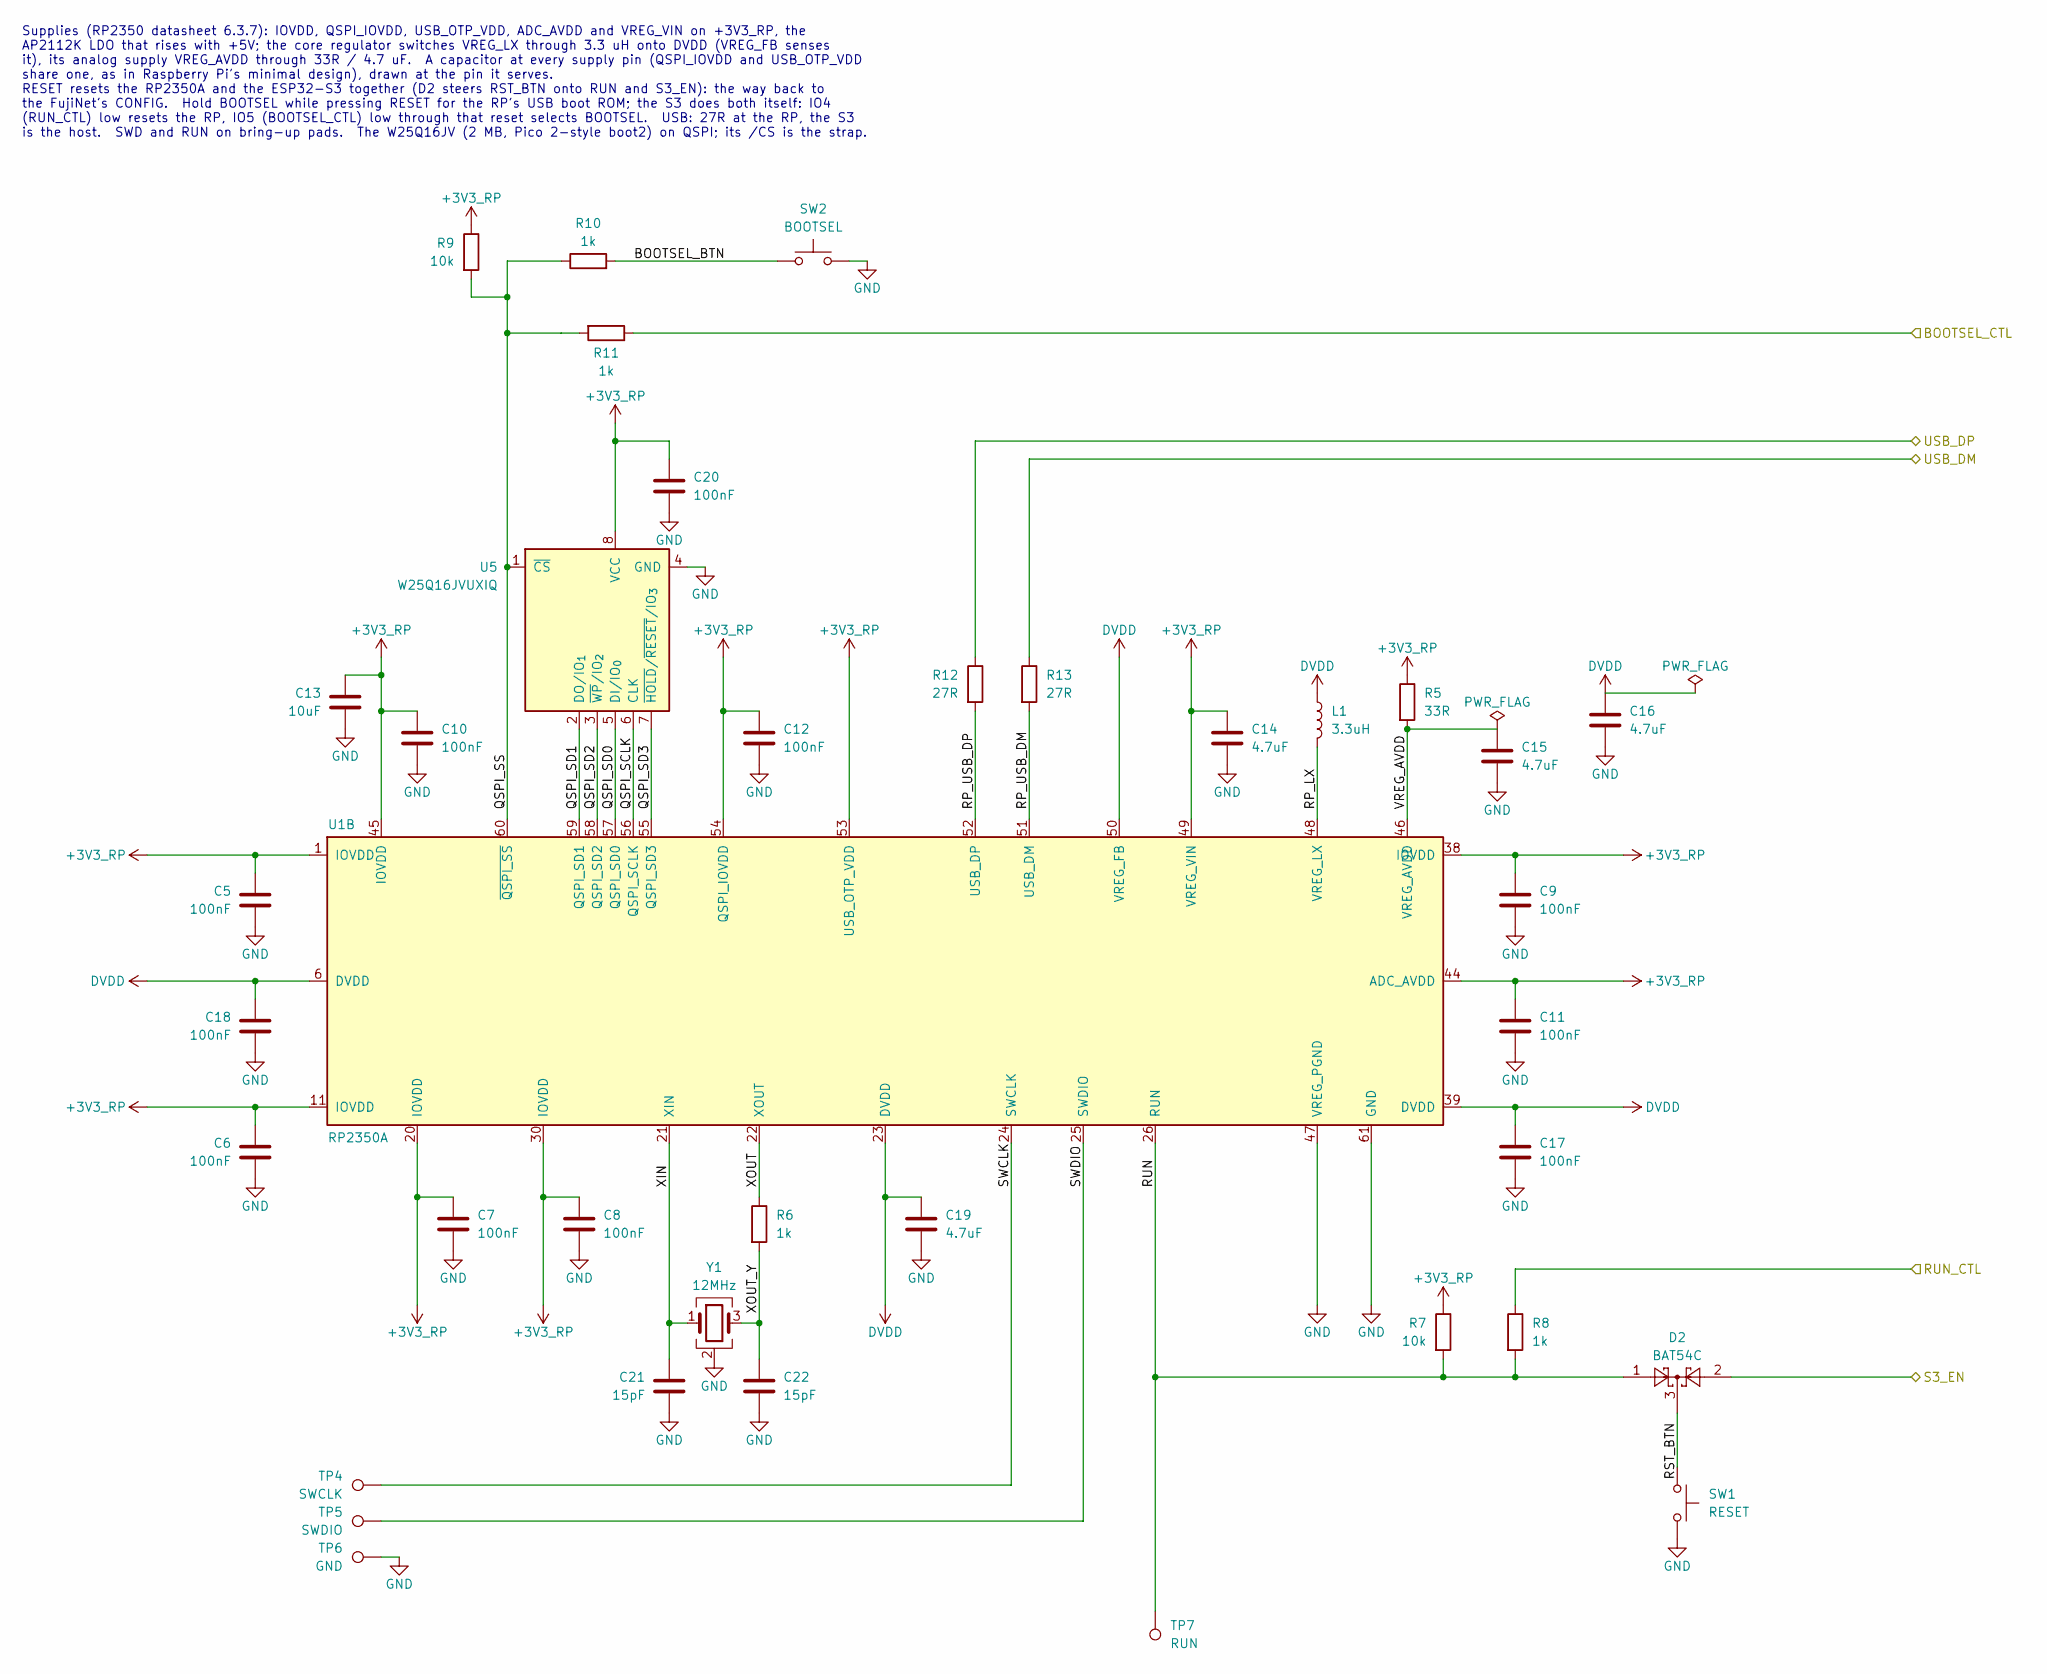
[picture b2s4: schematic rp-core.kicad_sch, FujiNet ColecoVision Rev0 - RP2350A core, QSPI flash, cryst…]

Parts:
C5, C6, C7, C12, C17, C18: 100nF; RPI_C0402; MPN CL05B104KO5NNNC; LCSC C1525
C8, C9, C10, C11, C20: 100nF; C_0603_1608Metric; MPN CC0603KRX7R9BB104; LCSC C14663
C13: 10uF; C_0603_1608Metric; MPN CL10A106KP8NNNC; LCSC C19702
C14, C16: 4.7uF; RPI_C0402_wide; MPN CL05A475MP5NRNC; LCSC C23733
C15, C19: 4.7uF; RPI_C0402; MPN CL05A475MP5NRNC; LCSC C23733
C21, C22: 15pF; C_0603_1608Metric; MPN CL10C150JB8NNNC; LCSC C1644
D2: BAT54C; SOT-23; MPN BAT54C,215; LCSC C37704
L1: 3.3uH; RPI_L_AOTA-B201610S3R3; MPN AOTA-B201610S3R3-101-T; LCSC C42411119
R5: 33R; RPI_R0402; MPN 0402WGF330JTCE; LCSC C25105
R6, R8, R10, R11: 1k; R_0603_1608Metric; MPN 0603WAF1001T5E; LCSC C21190
R7, R9: 10k; R_0603_1608Metric; MPN 0603WAF1002T5E; LCSC C25804
R12, R13: 27R; RPI_R0402; MPN 0402WGF270JTCE; LCSC C25100
SW1: RESET; SW_SPST_TS-1187A; MPN TS-1187A-B-A-B; LCSC C318884
SW2: BOOTSEL; SW_SPST_TS-1187A; MPN TS-1187A-B-A-B; LCSC C318884
TP4: SWCLK; TestPoint_Pad_D1.5mm
TP5: SWDIO; TestPoint_Pad_D1.5mm
TP6: GND; TestPoint_Pad_D1.5mm
TP7: RUN; TestPoint_Pad_D1.5mm
U1: RP2350A; RPI_RP2350A_QFN60; MPN RP2350A; LCSC C42411118
U5: W25Q16JVUXIQ; Winbond_USON-8-1EP_3x2mm_P0.5mm_EP0.2x1.6mm; MPN W25Q16JVUXIQ; LCSC C2843335
Y1: 12MHz; Crystal_SMD_3225-4Pin_3.2x2.5mm; MPN ABM8-272-T3; LCSC C20625731

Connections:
+3V3_RP: C5.1, C6.1, C7.1, C8.1, C9.1, C10.1, C11.1, C12.1, C13.1, C14.1, C20.1, R5.1, R7.1, R9.1, U1.1 (IOVDD), U1.11 (IOVDD), U1.20 (IOVDD), U1.30 (IOVDD), U1.38 (IOVDD), U1.44 (ADC_AVDD), U1.45 (IOVDD), U1.49 (VREG_VIN), U1.53 (USB_OTP_VDD), U1.54 (QSPI_IOVDD), U5.8 (VCC); also elsewhere on the board
/BOOTSEL_CTL: R11.1; also elsewhere on the board
/RUN_CTL: R8.1; also elsewhere on the board
/S3_EN: D2.2; also elsewhere on the board
/USB_DM: R13.1; also elsewhere on the board
/USB_DP: R12.1; also elsewhere on the board
/rp-core/BOOTSEL_BTN: R10.2, SW2.1
/rp-core/QSPI_SCLK: U1.56 (QSPI_SCLK), U5.6 (CLK)
/rp-core/QSPI_SD0: U1.57 (QSPI_SD0), U5.5 (DI/IO_{0})
/rp-core/QSPI_SD1: U1.59 (QSPI_SD1), U5.2 (DO/IO_{1})
/rp-core/QSPI_SD2: U1.58 (QSPI_SD2), U5.3 (~WP/IO_{2})
/rp-core/QSPI_SD3: U1.55 (QSPI_SD3), U5.7 (~HOLD/~RESET/IO_{3})
/rp-core/QSPI_SS: R9.2, R10.1, R11.2, U1.60 (~QSPI_SS), U5.1 (~CS)
/rp-core/RP_LX: L1.2, U1.48 (VREG_LX)
/rp-core/RP_USB_DM: R13.2, U1.51 (USB_DM)
/rp-core/RP_USB_DP: R12.2, U1.52 (USB_DP)
/rp-core/RST_BTN: D2.3, SW1.1
/rp-core/RUN: D2.1, R7.2, R8.2, TP7.1, U1.26 (RUN)
/rp-core/SWCLK: TP4.1, U1.24 (SWCLK)
/rp-core/SWDIO: TP5.1, U1.25 (SWDIO)
/rp-core/VREG_AVDD: C15.1, R5.2, U1.46 (VREG_AVDD)
/rp-core/XIN: C21.1, U1.21 (XIN), Y1.1
/rp-core/XOUT: R6.1, U1.22 (XOUT)
/rp-core/XOUT_Y: C22.1, R6.2, Y1.3
DVDD: C16.1, C17.1, C18.1, C19.1, L1.1, U1.6 (DVDD), U1.23 (DVDD), U1.39 (DVDD), U1.50 (VREG_FB)
GND: C5.2, C6.2, C7.2, C8.2, C9.2, C10.2, C11.2, C12.2, C13.2, C14.2, C15.2, C16.2, C17.2, C18.2, C19.2, C20.2, C21.2, C22.2, SW1.2, SW2.2, TP6.1, U1.47 (VREG_PGND), U1.61 (GND), U5.4 (GND), Y1.2 (G), Y1.4 (G); also elsewhere on the board

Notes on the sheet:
Supplies (RP2350 datasheet 6.3.7): IOVDD, QSPI_IOVDD, USB_OTP_VDD, ADC_AVDD and VREG_VIN on +3V3_RP, the AP2112K LDO that rises with +5V; the core regulator switches VREG_LX through 3.3 uH onto DVDD (VREG_FB senses it), its analog supply VREG_AVDD through 33R / 4.7 uF. A capacitor at every supply p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
